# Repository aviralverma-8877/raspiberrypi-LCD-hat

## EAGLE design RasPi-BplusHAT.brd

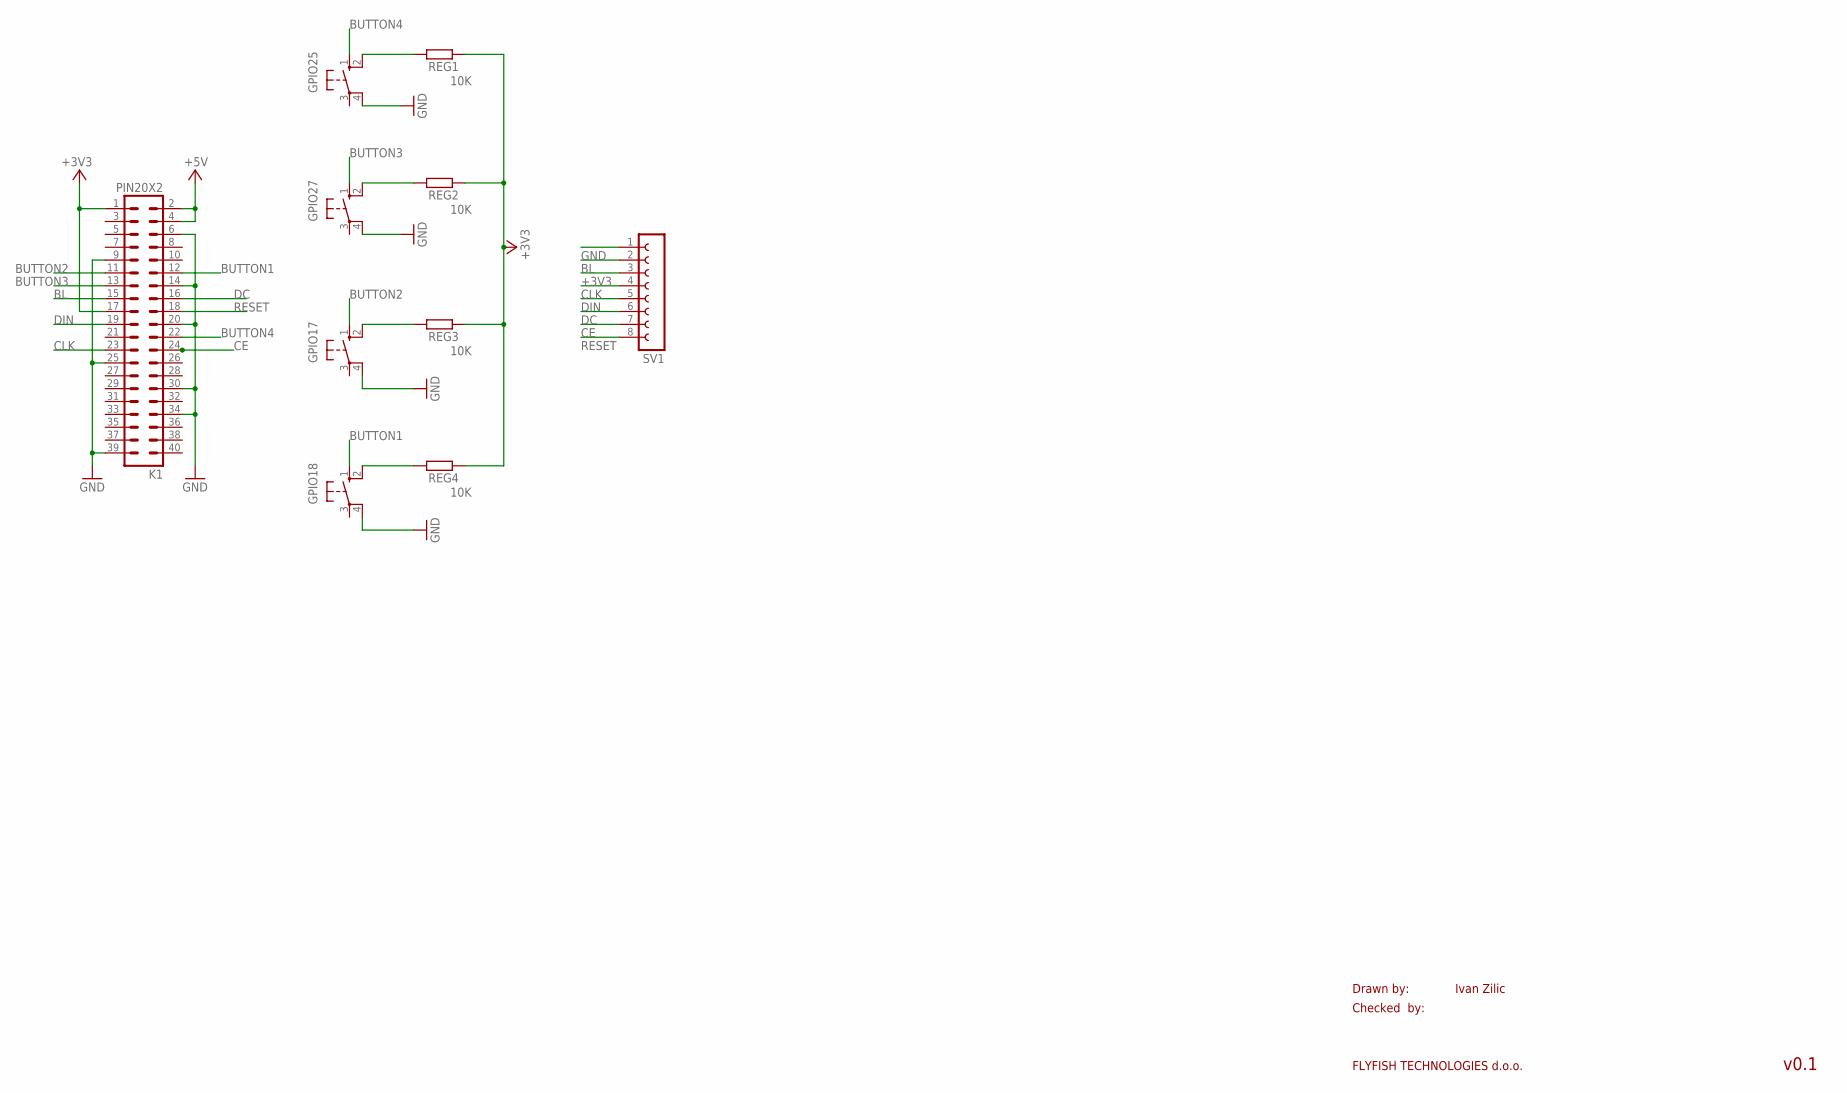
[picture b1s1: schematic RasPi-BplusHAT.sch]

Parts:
GPIO17, GPIO18, GPIO25, GPIO27: 10-XX; B3F-10XX
K1: PIN20X2; PIN_20X2
REG1, REG2, REG3, REG4: 10K; 0204/7
SV1: FE08-1; FE08

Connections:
+3V3: K1.1, K1.17, REG1.1, REG2.1, REG3.1, REG4.1, SV1.3
+5V: K1.2, K1.4
BL: K1.15, SV1.2
BUTTON1: GPIO18.1 (S), K1.12
BUTTON2: GPIO17.1 (S), K1.11
BUTTON3: GPIO27.1 (S), K1.13
BUTTON4: GPIO25.1 (S), K1.22
CE: K1.24, SV1.7
CLK: K1.23, SV1.4
DC: K1.16, SV1.6
DIN: K1.19, SV1.5
GND: GPIO17.4 (P1), GPIO18.4 (P1), GPIO25.4 (P1), GPIO27.4 (P1), K1.6, K1.9, K1.14, K1.20, K1.25, K1.30, K1.34, K1.39, SV1.1
unnamed: GPIO25.2 (S1), REG1.2
unnamed: GPIO27.2 (S1), REG2.2
unnamed: GPIO17.2 (S1), REG3.2
unnamed: GPIO18.2 (S1), REG4.2
RESET: K1.18, SV1.8

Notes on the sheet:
Drawn by:
Checked by:
FLYFISH TECHNOLOGIES d.o.o.
Ivan Zilic
v0.1

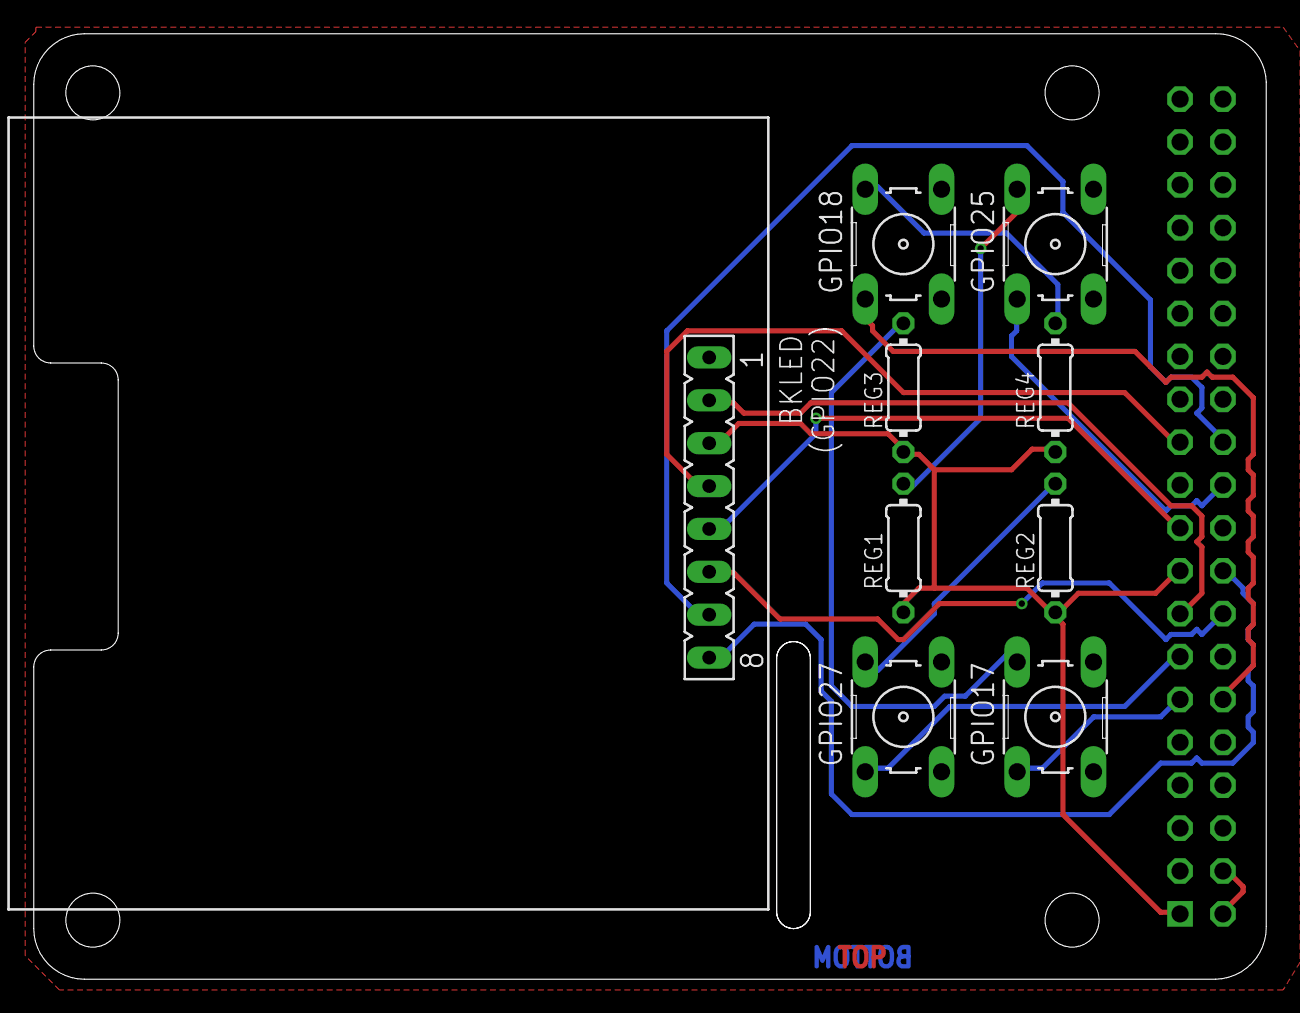
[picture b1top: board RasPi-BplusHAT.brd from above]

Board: 2 copper layers, 73.0 x 56.0 mm, 10 parts (1 on the bottom side), 17 nets.

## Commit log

2019-08-29 files added
2019-09-17 Fixes
2021-11-23 Ground polygon added
2023-08-15 Auto routed
